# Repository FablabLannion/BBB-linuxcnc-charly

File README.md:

BBB-linuxcnc-charly
===================

add to machinekit distrib components (eqep &amp; pwm) to be able to control servo motors. This type of motors are used on our cnc : CharlyRobot

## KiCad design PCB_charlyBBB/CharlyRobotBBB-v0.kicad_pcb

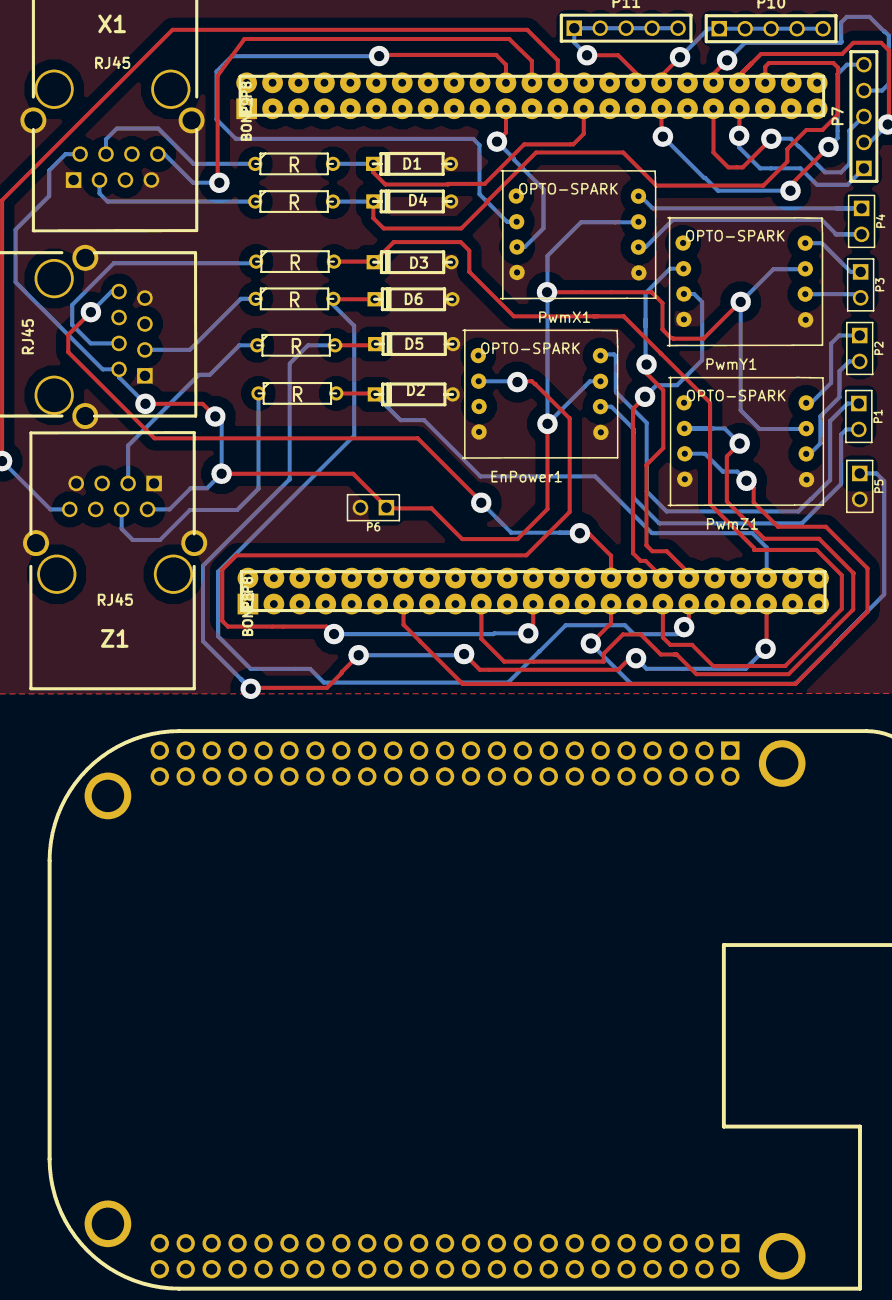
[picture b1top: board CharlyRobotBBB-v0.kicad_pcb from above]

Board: 2 copper layers, 31 parts (0 on the bottom side), 40 nets.

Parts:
D1, D2, D3, D4, D5, D6: ZENER; D3
EnPower1: OPTO-SPARK; opto-spark-dim-ok
P1, P2, P3, P4, P5, P6: CONN_2; PIN_ARRAY_2X1
P7, P10, P11: CONN_5; PIN_ARRAY_5x1
P8, P9: BONE_P8; BoneHdr
PwmX1: OPTO-SPARK; opto-spark-dim-ok
PwmY1: OPTO-SPARK; opto-spark-dim-ok
PwmZ1: OPTO-SPARK; opto-spark-dim-ok
R1, R2, R3, R4, R5, R6: R; R3
U1: BEAGLEBONE BLACK; BEAGLEBONEBLACK
X1: RJ45; RJ45_shield
Y1: RJ45; RJ45_shield
Z1: RJ45; RJ45_shield

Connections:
+5V: EnPower1.6, P6.1, PwmX1.6, PwmY1.6, PwmZ1.6, X1.2, Y1.2, Z1.2
GND: D1.1, D2.1, D3.1, D4.1, D5.1, D6.1, EnPower1.4, EnPower1.8, P5.2, P6.2, P9.1, PwmX1.4, PwmX1.8, PwmY1.4, PwmY1.8, PwmZ1.4, PwmZ1.8, X1.1, X1.7, X1.13, Y1.1, Y1.7, Y1.13, Z1.1, Z1.7, Z1.13
unnamed: D5.2, P8.41, R4.2
unnamed: R6.1, Y1.3
unnamed: R1.1, X1.4
unnamed: R2.1, X1.3
unnamed: D4.2, P9.42, R2.2
unnamed: R5.1, Y1.4
unnamed: D3.2, P8.33, R5.2
unnamed: D2.2, P8.42, R3.2
unnamed: P9.24, X1.8
unnamed: D1.2, P9.27, R1.2
unnamed: D6.2, P8.35, R6.2
unnamed: R4.1, Z1.3
unnamed: R3.1, Z1.4
unnamed: P8.34, PwmY1.3
unnamed: P9.21, PwmX1.3
unnamed: P8.30, Y1.8
unnamed: P4.2, PwmX1.7
unnamed: P4.1, PwmX1.5
unnamed: P3.2, PwmY1.7
unnamed: P3.1, PwmY1.5
unnamed: P2.2, PwmZ1.7
unnamed: P2.1, PwmZ1.5
unnamed: EnPower1.7, P1.2
unnamed: EnPower1.5, P1.1
unnamed: P9.34, P10.1, P10.2, P10.3, P10.4, P10.5
unnamed: P7.5, P9.33
unnamed: P7.4, P9.38
unnamed: P7.3, P9.37
unnamed: P7.1, P9.39
unnamed: P9.32, P11.1, P11.2, P11.3, P11.4, P11.5
unnamed: P5.1, P8.29
unnamed: P7.2, P9.40
unnamed: P8.36, PwmY1.2
unnamed: P9.22, PwmX1.2
unnamed: P9.26, Z1.8
unnamed: EnPower1.2, P8.23
unnamed: P8.13, PwmZ1.3
unnamed: P8.19, PwmZ1.2

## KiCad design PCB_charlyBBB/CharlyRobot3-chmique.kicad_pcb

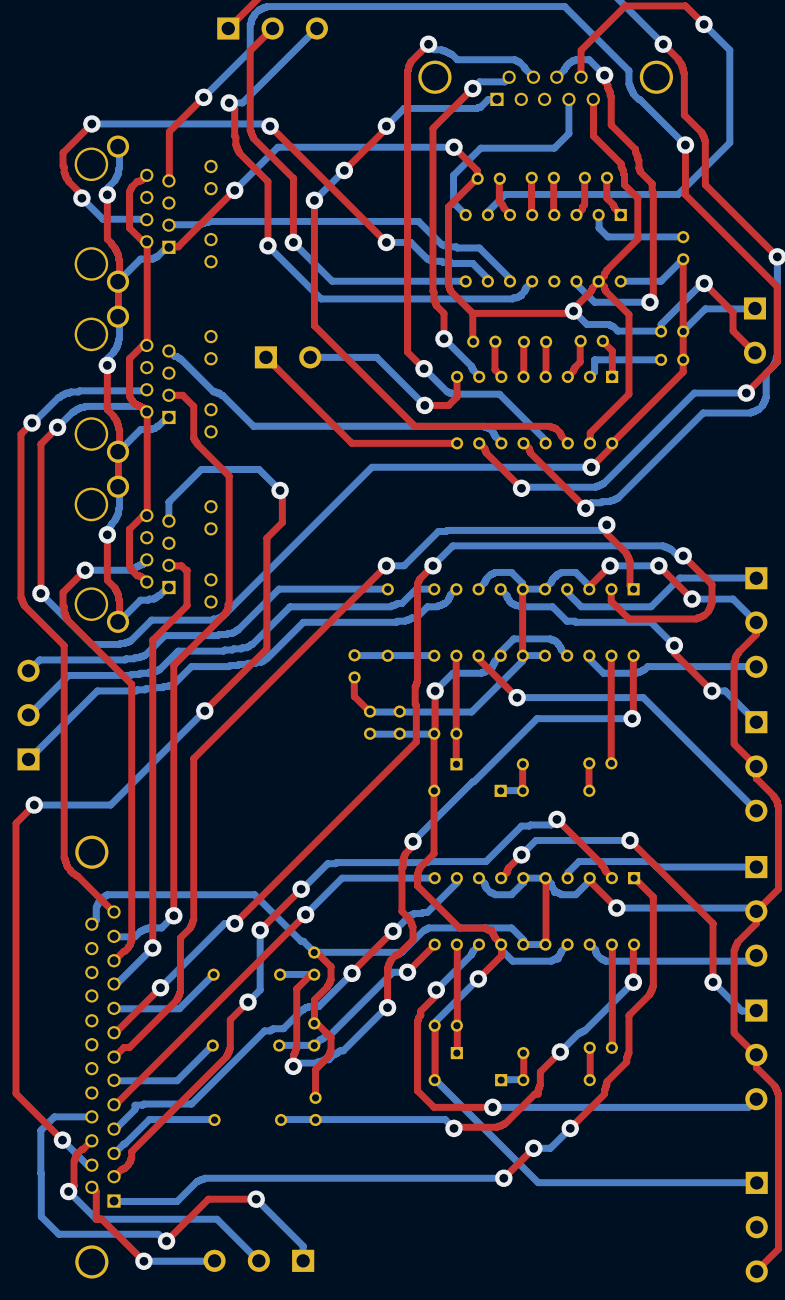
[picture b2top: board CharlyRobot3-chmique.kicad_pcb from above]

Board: 2 copper layers, 48 parts (0 on the bottom side), 72 nets.

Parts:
C1, C2, C3, C4, C5, C6, C9, C10, C11, C12, C13, C14, C15, C16, C17, C18, C19, C20, C21: C; C1
D1, D2, D3, D4: DIODE; D3
IC1, IC2: L6205N; DIP-20__300
J1, J2, J4: RJ45; RJ45_TRANSFO
J3: DB25; DB25FC
J5: DB9; DB9FC
K1, K2, K3, K4, K5, K6, K7, K8: CONN_3; bornier3
P1, P2: CONN_2; bornier2
R1, R2, R3, R4, R5, R6: R; R3
U1, U2: MAX232; DIP-16__300

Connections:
+5V: C15.1, C16.1, C20.1, J1.2, J1.8, J2.2, J2.8, J4.2, J4.8, P1.1, U1.16, U2.16
DGND: C15.2, C17.1, C21.1, J1.1, J1.13, J2.1, J2.13, J4.1, J4.13, J5.5, P1.2, U1.15, U2.15
GND: C1.1, C2.1, C5.1, C6.1, C9.1, C11.1, IC1.3, IC1.5, IC1.6, IC1.8, IC1.15, IC1.16, IC2.3, IC2.5, IC2.6, IC2.8, IC2.15, IC2.16, J3.25, K1.2, K2.2, K3.2, K4.2, K5.3
unnamed: J3.3, R2.1
unnamed: IC2.4, K2.1
unnamed: IC1.1, J3.1
unnamed: IC1.2, J3.2
unnamed: IC1.9, J3.4
unnamed: IC1.10, J3.5
unnamed: J3.6, R3.1
unnamed: C10.1, R6.2
unnamed: C11.2, IC2.20, R5.2
unnamed: IC2.1, J3.7
unnamed: IC2.2, J3.8
unnamed: J3.9, R5.1
unnamed: C10.2, IC2.19
unnamed: J3.10, J4.3
unnamed: J3.11, J4.4
unnamed: J3.15, J4.7
unnamed: C6.2, IC1.20, R2.2
unnamed: IC1.4, K1.1
unnamed: C4.2, IC1.19
unnamed: C4.1, R1.2
unnamed: IC2.18, K2.3
unnamed: D3.2, D4.1, R6.1
unnamed: IC2.13, K4.3
unnamed: IC2.7, K4.1
unnamed: C9.2, IC2.11, R4.2
unnamed: IC2.10, K7.2
unnamed: K7.3, R4.1
unnamed: IC2.9, K7.1
unnamed: J3.16, K8.2
unnamed: J3.17, K8.1
unnamed: J5.3, U1.13
unnamed: J5.8, U1.14
unnamed: J1.7, U2.10
unnamed: J5.6, U2.7
unnamed: J5.9, U1.7
unnamed: J3.14, K8.3
unnamed: P2.1, U2.9
unnamed: P2.2, U2.8
unnamed: K6.3, U1.12
unnamed: J5.7, U2.13
unnamed: J5.4, U1.8
unnamed: K6.2, U1.9
unnamed: K6.1, U2.12
unnamed: J2.4, J3.13
unnamed: C18.1, U2.1
unnamed: C18.2, U2.3
unnamed: C19.1, U2.4
unnamed: C19.2, U2.5
unnamed: C13.2, U1.5
unnamed: C13.1, U1.4
unnamed: C12.2, U1.3
unnamed: C12.1, U1.1
unnamed: C17.2, U1.6
unnamed: C21.2, U2.6
unnamed: J2.3, J3.12
unnamed: J1.3, U1.11
unnamed: J2.7, U2.11
unnamed: J5.1, U2.14
unnamed: J1.4, U1.10
unnamed: C20.2, U2.2
unnamed: C16.2, U1.2
unnamed: IC1.7, K3.1
unnamed: IC1.18, K1.3
unnamed: IC1.13, K3.3
unnamed: C3.2, D2.2, IC1.12
unnamed: C5.2, IC1.11, R3.2
unnamed: D1.2, D2.1, R1.1
unnamed: C14.2, D4.2, IC2.12
VSS: C1.2, C2.2, C3.1, C14.1, D1.1, D3.1, IC1.14, IC1.17, IC2.14, IC2.17, K5.1

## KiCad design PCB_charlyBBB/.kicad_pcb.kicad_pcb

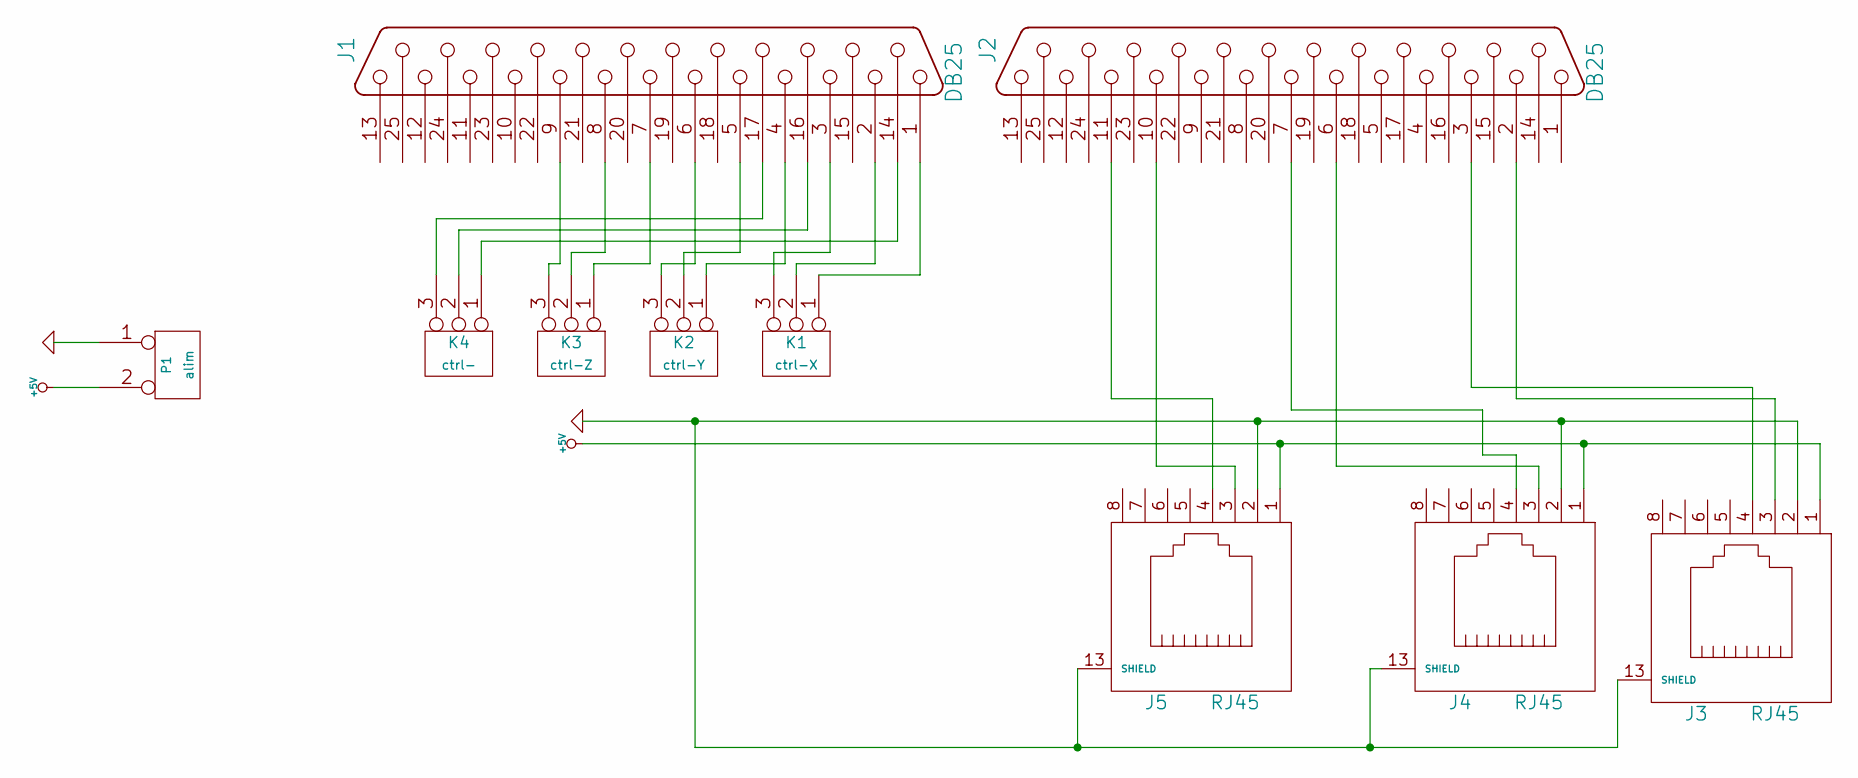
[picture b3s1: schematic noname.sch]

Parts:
J1, J2: DB25
J3, J4, J5: RJ45
K1: ctrl-X
K2: ctrl-Y
K3: ctrl-Z
K4: ctrl-
P1: alim

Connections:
+5V: J3.1, J4.1, J5.1, P1.2 (PM)
GND: J3.2, J3.13 (SHIELD), J4.2, J4.13 (SHIELD), J5.2, J5.13 (SHIELD), P1.1
unnamed: J1.4, K2.1
unnamed: J1.5, K2.2 (PM)
unnamed: J1.6, K2.3
unnamed: J1.7, K3.1
unnamed: J1.8, K3.2 (PM)
unnamed: J1.9, K3.3
unnamed: J1.14, K4.1
unnamed: J1.16, K4.2 (PM)
unnamed: J1.1, K1.1
unnamed: J1.2, K1.2 (PM)
unnamed: J1.3, K1.3
unnamed: J2.11, J5.4
unnamed: J2.6, J4.3
unnamed: J2.7, J4.4
unnamed: J2.10, J5.3
unnamed: J1.17, K4.3
unnamed: J2.2, J3.3
unnamed: J2.3, J3.4

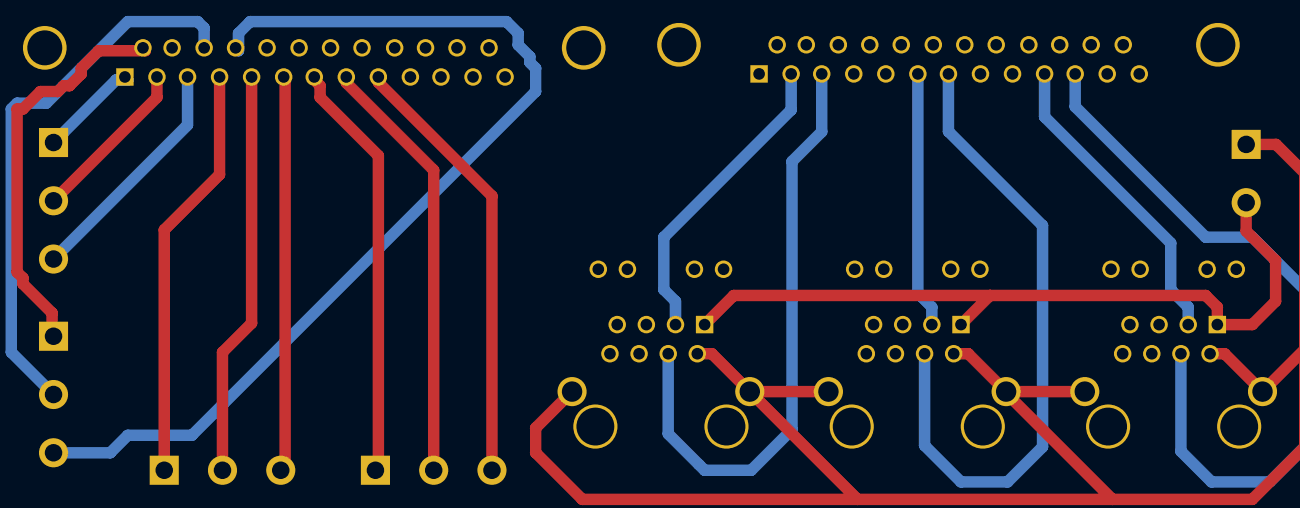
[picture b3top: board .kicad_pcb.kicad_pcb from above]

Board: 2 copper layers, 10 parts (0 on the bottom side), 20 nets.

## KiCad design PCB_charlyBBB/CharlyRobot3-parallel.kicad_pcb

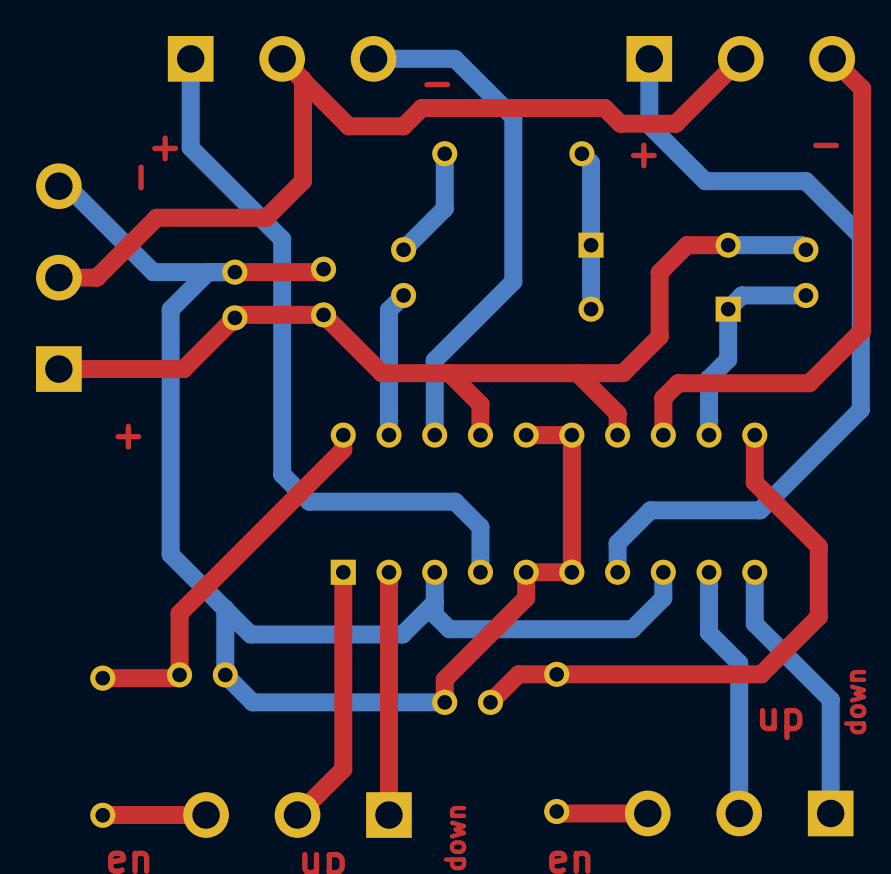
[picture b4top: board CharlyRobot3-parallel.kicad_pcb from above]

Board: 2 copper layers, 17 parts (0 on the bottom side), 19 nets.

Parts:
C1, C2, C3, C4, C5, C6: C; C1
D1, D2: DIODE; D3
IC1: L6205N; DIP-20__300
K1: in-chA; bornier3
K2: in-chB; bornier3
K3: pw-out chA; bornier3
K4: chB; bornier3
K5: CONN_3; bornier3
R1, R2, R3: R; R3

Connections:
GND: C1.1, C2.1, C5.1, C6.1, IC1.3, IC1.5, IC1.6, IC1.8, IC1.15, IC1.16, K5.3
GNDPWR: K3.2, K4.2, K5.2
unnamed: C6.2, IC1.20, R2.2
unnamed: C4.1, R1.2
unnamed: IC1.7, K4.1
unnamed: IC1.4, K3.1
unnamed: D1.2, D2.1, R1.1
unnamed: C4.2, IC1.19
unnamed: IC1.1, K1.2
unnamed: IC1.9, K2.2
unnamed: IC1.10, K2.1
unnamed: K2.3, R3.1
unnamed: K1.3, R2.1
unnamed: IC1.2, K1.1
unnamed: C3.2, D2.2, IC1.12
unnamed: IC1.18, K3.3
unnamed: IC1.13, K4.3
unnamed: C5.2, IC1.11, R3.2
VSS: C1.2, C2.2, C3.1, D1.1, IC1.14, IC1.17, K5.1

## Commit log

2014-12-31 update repository
2014-12-31 add rt_drivers
2014-12-31 add linuxcnc_component
2015-04-01 grosse mise à jour... faut que je commit plus souvent
2015-04-01 ajout conf linuxcnc
2015-04-01 ajout presentation
2015-09-09 parcequ il en faut un
